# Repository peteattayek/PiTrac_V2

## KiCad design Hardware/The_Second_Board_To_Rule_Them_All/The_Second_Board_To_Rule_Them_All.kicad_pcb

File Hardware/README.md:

# PiTrac V2 — Hardware

KiCad design and RP2354 firmware for the PiTrac launch monitor controller board:
*"The Second Board To Rule Them All"*, Rev V1.

> **New to this repo?** Start with [`../DEVELOPER_GUIDE.md`](../DEVELOPER_GUIDE.md). It covers
> the repo map, the full pinout, how the firmware is built and why, and what is not done yet.

The board detects a golf ball crossing an IR light curtain, measures its speed from
the beam transit time, triggers two Mira220 global-shutter cameras, and fires a
high-power IR strobe in a precisely timed burst so each camera freezes the ball
~10 times in a single exposure. A Raspberry Pi 5 rides on top — powered *by* this
board through the 40-pin header — and handles image pull and analysis.

**The RP2354 owns everything with microsecond timing requirements. The Pi owns
everything with pixels.**

---

## Layout

```
Hardware/
├── The_Second_Board_To_Rule_Them_All.md     ← design document: theory of operation,
│                                              subsystem detail, test points, pin map
├── The_Second_Board_To_Rule_Them_All/       ← KiCad 10 project, 8 sheets
│   ├── *.kicad_sch, *.kicad_pcb
│   ├── *.net                                 netlist export (firmware is verified against this)
│   └── jlcpcb/production_files/              gerbers + BOM + CPL as sent to fab
└── firmware/                                ← RP2354B firmware, C / Pico SDK 2.x
```

`../HARDWARE_REFERENCE.md` (repo root) is **generated** from the netlist by
`firmware/tools/netlist_report.py`. Regenerate it rather than editing it.

### Camera calibration

[Calibration/README.md](Calibration/README.md) contains the camera-distortion
procedure, A4/Letter ChArUco print templates, capture checklist, and session/result
records. Use a separate calibration for each identified physical camera/lens
stack at its final filter, illumination, and locked-focus state. Digital target
checks do not establish physical print quality or calibrated camera coefficients.

### Firmware documents, in reading order

| File | What it is |
|---|---|
| **`firmware/START_HERE.md`** | **Start here if you have never built Pico firmware.** Toolchain install, build, flash, first CLI commands. Assumes no C or embedded experience. |
| `firmware/HANDOFF.md` | Working conventions, safety rules, tooling traps and hard-won measurement lessons, for anyone taking over the bench work. |
| `firmware/PROGRESS.md` | **The living record.** What is done, open questions with where each gets resolved, recent bench measurements, the decisions behind the design, and the code-audit backlog. §0 and §10 hold the live status. Read before changing anything. |
| `firmware/PROGRESS_ARCHIVE.md` | Closed history moved verbatim out of PROGRESS.md (older measurement log, superseded resume blocks, dated Phase 3 results). Nothing in it is current status. |
| `firmware/ARCHITECTURE.md` | Hardware-offload audit — what runs on PIO/PWM/DMA versus the CPU, and why. |
| `firmware/BRINGUP_NEW_BOARD.md` | **The driver for a newly assembled board.** Only the per-board steps, in order, with a sign-off table. |
| `firmware/BENCH.md` | Bring-up procedures, phases 0 → 1c. |
| `firmware/BENCH_P2_BEAM.md` | Phase 2 — beam carrier and phase-locked demodulator. |
| `firmware/BENCH_P3_DETECT.md` | Phases 3 & 4 — photodiode chain and trigger selection. |
| `firmware/BENCH_P5_P7_MIC_CAMERA.md` | Phases 5 & 7 — microphone and cameras. |
| `firmware/BENCH_P6_STROBE.md` | Phase 6 — ⚠ 9 A pulses, linear-mode FET. Read fully before powering. |
| `firmware/BENCH_P8_PI.md` | Phase 8 — real Pi 5 integration and clean-shutdown acceptance. |
| `firmware/NEXT_BOARD_REV.md` | Hardware change requests (CR-xx) for the next board spin. |
| `firmware/SETUP.md` | Toolchain detail and the manual (non-VS-Code) install path. |

---

## Status

Bring-up is staged, and each phase is independently provable on the bench before
the next begins. **The live status is always `firmware/PROGRESS.md` §0 and the top
block of §10** — this table is a summary as of 2026-10-05.

| Phase | |
|---|---|
| 0 · toolchain, CLI, ADC/DMA capture | ✅ |
| 0.5 · rails, boost, virtual ground | ✅ |
| 1 · power button, latch, supply guards | ✅ (Test 6, stale power requests: ✅ owner-reported 2026-09-28) |
| 1b · Pi soft-shutdown vs. a simulated Pi | ✅ |
| 1c · panel indicators | ✅ |
| 2 · beam carrier + demod phase lock | ✅ |
| 3 · photodiode chain and calibration | 🟡 §3.1–3.6 done on board 3; first real ball waveform passed; comparator timing and the 20-pass set are open |
| 4 · trigger-source experiment | 🟡 firmware written, bench not started |
| 5 · microphone | 🟡 front end validated; no onset-detection or veto firmware yet |
| 6 · strobe | 🟡 **6a/6b dry tests PASS on board 1 (2026-10-06)** — U5 clamp 135 µs, PIO timing, schedule, A7, interlock, gate DAC. **6c/6d live-current firmware written 2026-10-07** (guarded: staircase, 70 % ceiling, ADC0 readback per firing, overcurrent/stuck-on faults, watchdog); TP3 loop stability PASS 2026-10-08; 6c on board 1 up to 24 % after a gate-drive rework (CR-23); **6d PASS 2026-10-15**; next is the ADC0 readback fix |
| 7 · cameras | ❌ no firmware yet; blocked on the 1.8 V I/O translator (CR-09) |
| 8 · Pi integration | 🟡 power and shutdown handshake done; UART protocol not written |

---

## Safety rules that outrank convenience

1. **No Pi 5 on J8 until Phase 7c.** The +5 V latch *is* the Pi's power switch, and any
   RP2354 reset — SW2, `reset`, `bootsel`, the watchdog, a brownout — opens it: a hard power
   cut, not a reboot.
2. **`PULSE_LIMIT_DISABLE` (GPIO27) stays 0.** It defeats the strobe hardware
   watchdog. It is written in exactly one place in the firmware and there is
   deliberately no CLI path to it.
3. **Never run the +5 V rail from USB power.** Two independent guards enforce this;
   both exist because the failure mode is a Pi 5 fed through a 1 A diode.
4. **Do not connect J4 (cameras).** The Mira220 I/O is 1.8 V with no 3.3 V tolerance
   (answered 2026-08-14). J4 needs a level translator first — `firmware/NEXT_BOARD_REV.md`
   CR-09.
5. **Nothing conductive near the photodiode D12.** Its cathode sits at 36 V; foil across it
   destroyed an op-amp on board 1.

---

## Building the firmware

```
cd firmware
cmake -B build -G Ninja -DCMAKE_BUILD_TYPE=Release
cmake --build build
```

Needs Pico SDK **2.1+** (the project pins 2.3.0) and an ARM toolchain — `firmware/SETUP.md`
covers both, and the VS Code Pico extension installs everything itself if you would rather
not. The extension keeps its tools in `~/.pico-sdk` and does **not** put them on `PATH`;
see `firmware/HANDOFF.md` §4 for the command-line build.

The board is an **RP2354B**: RP2350B core, 48 GPIO, 2 MB stacked internal flash,
**ARM** (not RISC-V). `CMakeLists.txt` forces the correct board and there is a
compile-time assert that fails loudly if anything overrides it.

---

## Design corrections

The design document predates bring-up, and several of its numbers were superseded by
measurement. The evidence is in `firmware/PROGRESS.md`; the full list is in
[`../DEVELOPER_GUIDE.md`](../DEVELOPER_GUIDE.md) §4. The ones most worth knowing:

- **The virtual ground is not 2.50 V.** R75/R76 = 10K/10K makes it literally
  +5VA ÷ 2 — measured **2.59 V** on the 5.2 V rail. It also moves with the rail (CR-02).
- **The one-shot clamp is 122.68 µs** (U9, measured in Phase 2c), not the .md's 113 µs
  and not the 86 µs the datasheet's K ≈ 0.7 predicted. U5, the strobe one-shot, is still
  unmeasured.
- **`cal_demod_phase()` in §13.8 cannot work as written** — it samples after a
  0.66 s high-pass with a *static* reflector, so it reads noise at every phase. The
  firmware's chopped-beam `cal demod` replaces it.
- **RPI5_SHUTDOWN is active-low**, matching the default `gpio-shutdown` overlay —
  confirmed on hardware as a 200 ms low pulse. The .md pseudocode is backwards.
- **The PWM slice numbers in the .md are RP2040 numbering.** On the RP2350B the beam
  carrier is slice 7B, the demod clock 11B and the gate DAC 6A — which collides with the
  ready LED (CR-01).
- **`HPF_Toggle` low is TRACK**, not HOLD.

---

## License

See [`../LICENSING.md`](../LICENSING.md). Board design files are **CERN-OHL-S v2**
(`../LICENSES/CERN-OHL-S-2.0.txt`); firmware and host tools are **GPL-3.0-or-later**
(`../LICENSE`).

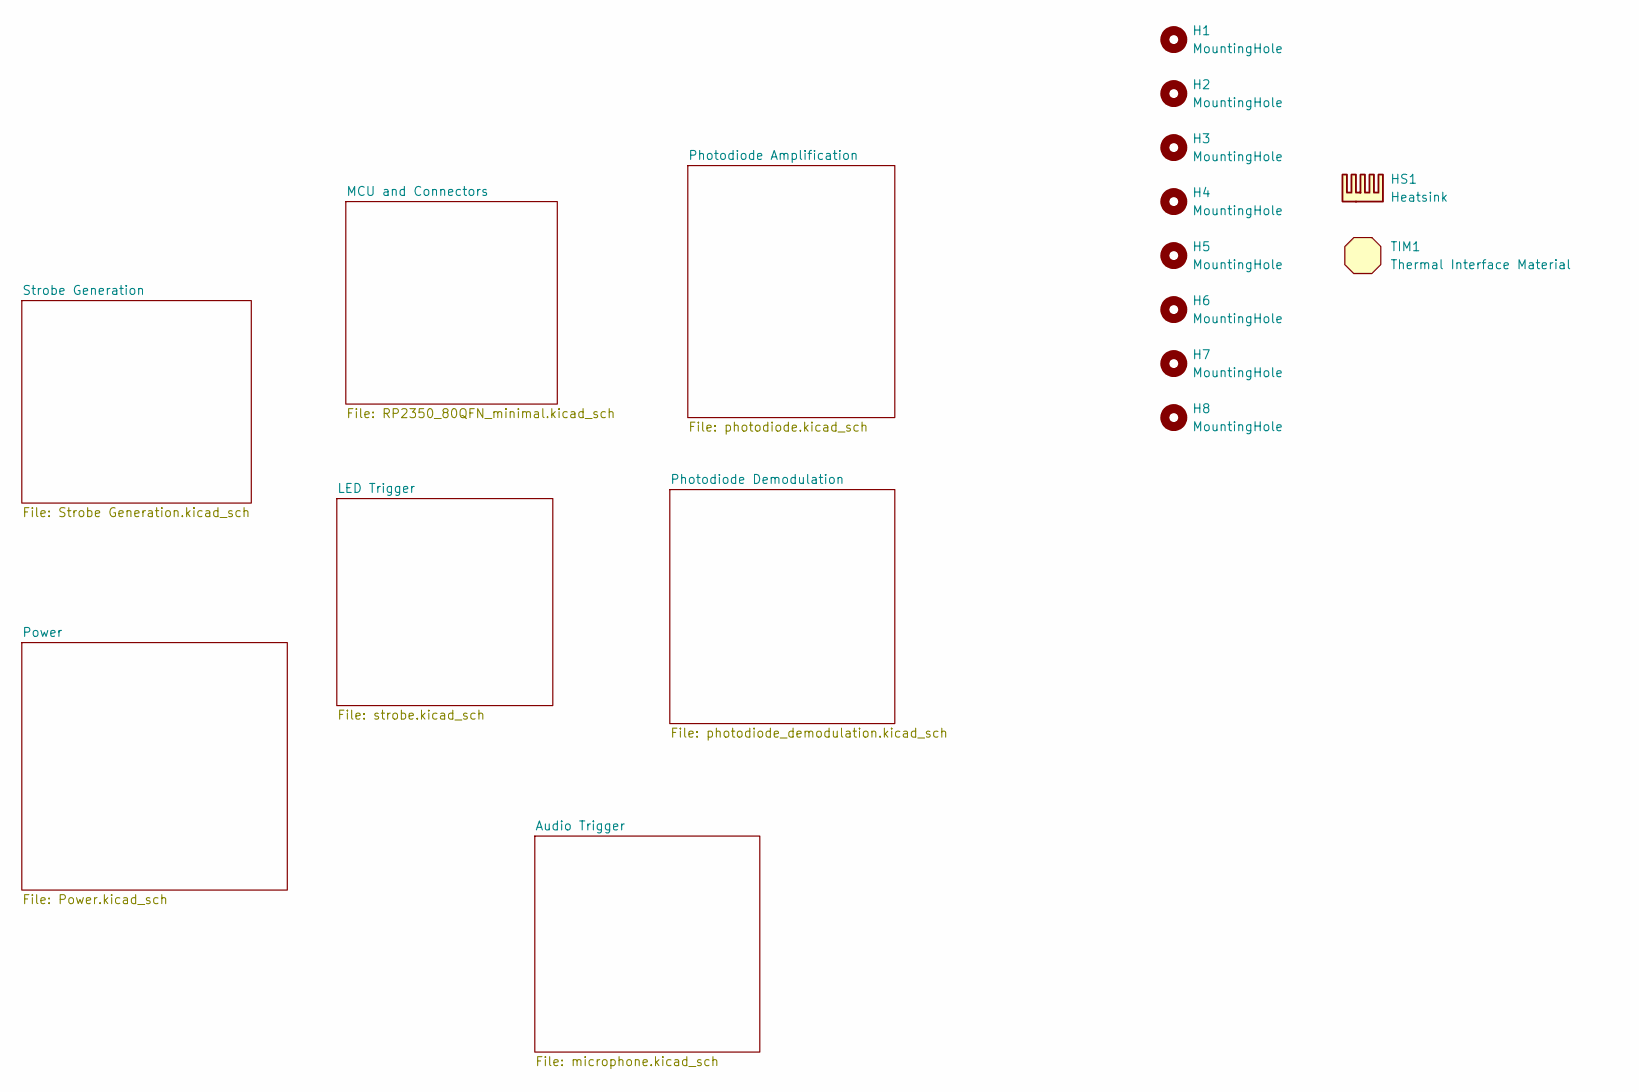
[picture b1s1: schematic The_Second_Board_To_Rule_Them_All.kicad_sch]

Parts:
H1, H2, H7, H8: MountingHole; MountingHole_2.2mm_M2
H3, H4, H5, H6: MountingHole; MountingHole_2.7mm_M2.5
HS1: Heatsink; Ratings <= 27 C/W; MPN HSB09-212115
TIM1: Thermal Interface Material; MPN TG-T1000-20-20-0.25-5PT

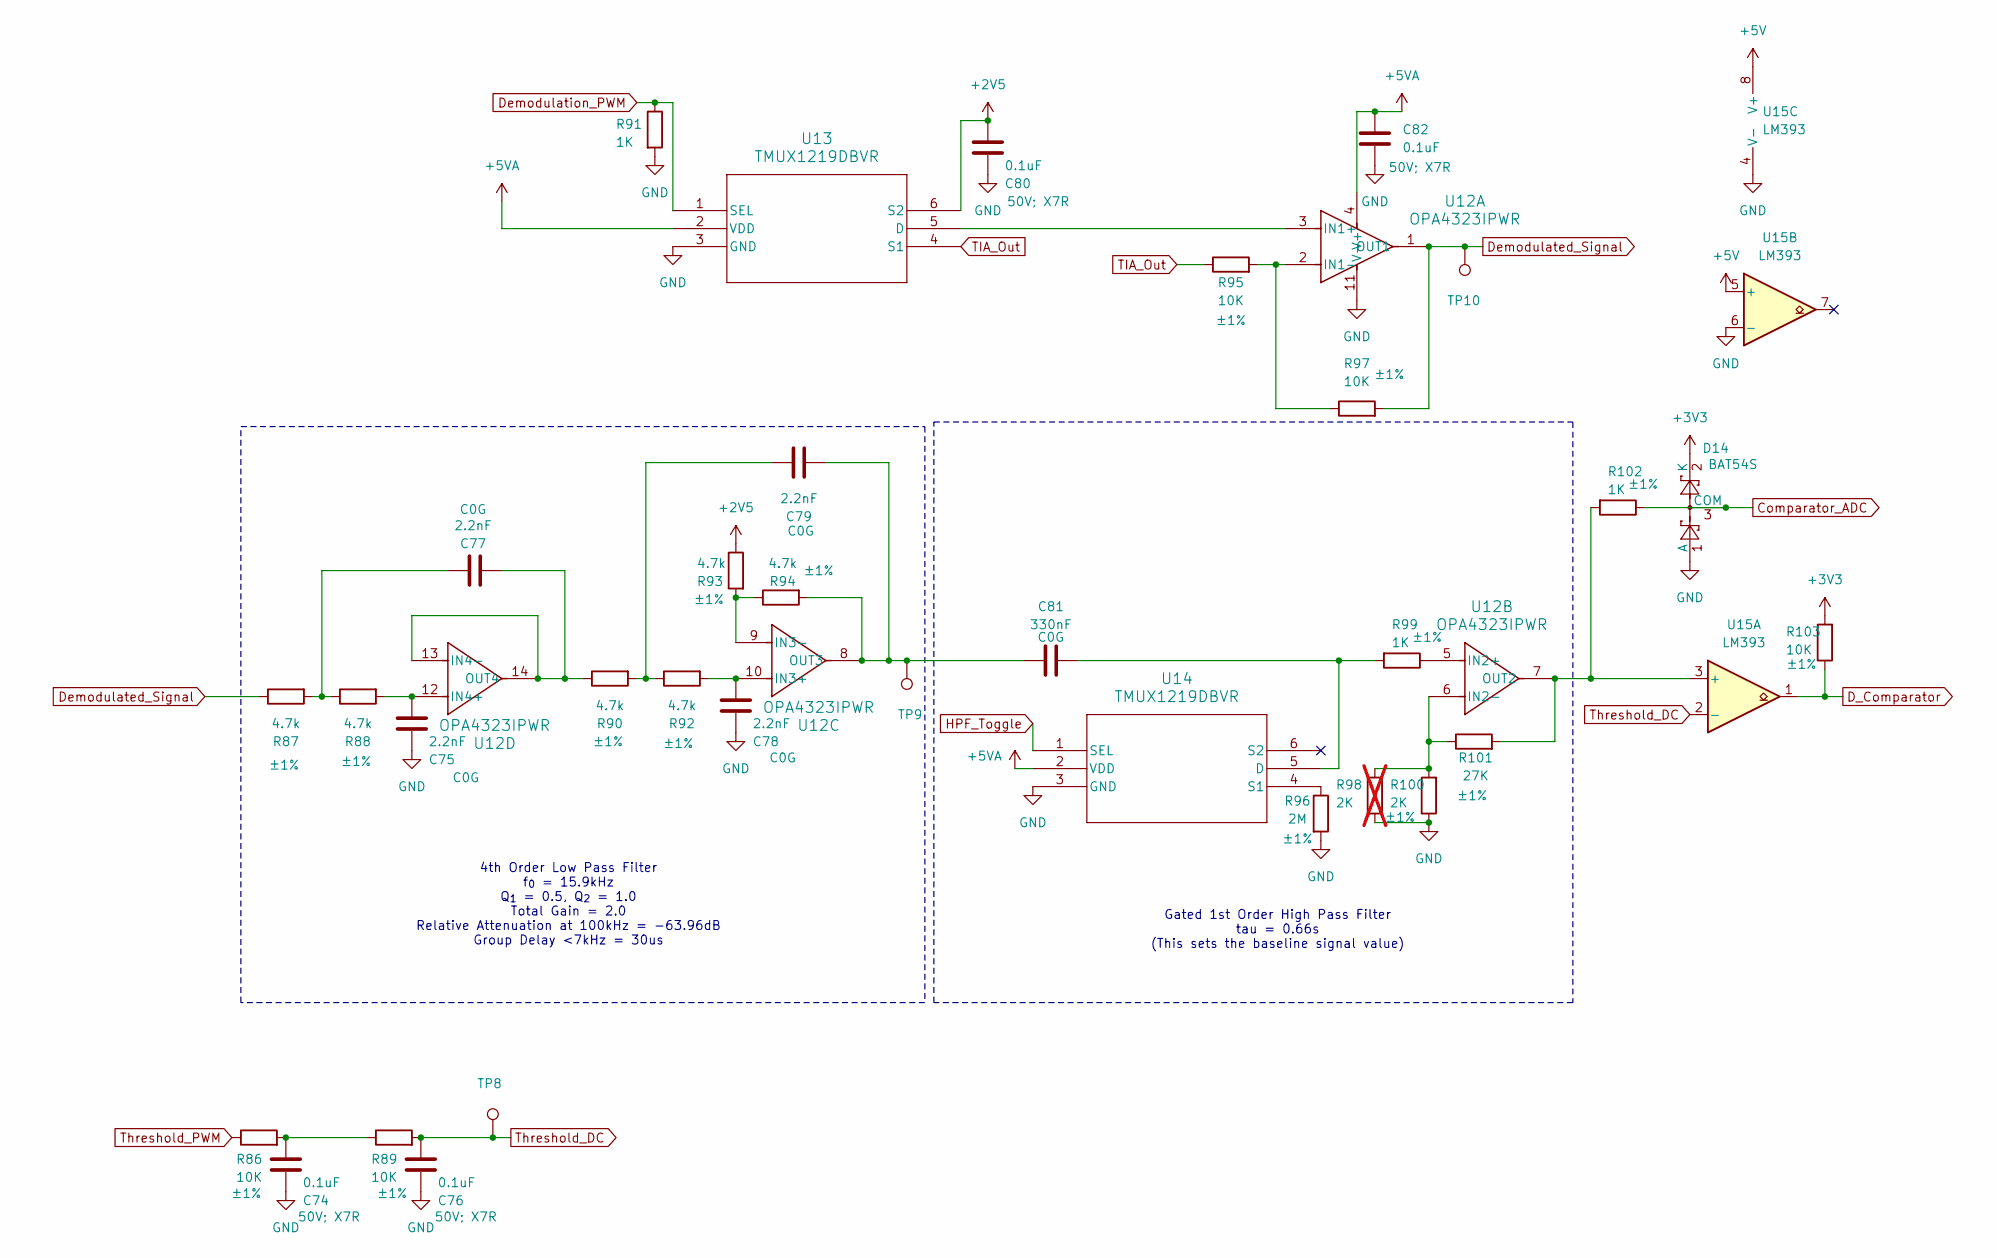
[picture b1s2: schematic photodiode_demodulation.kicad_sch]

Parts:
C74, C76, C80, C82: 0.1uF; C_0402_1005Metric; Ratings 50V; X7R; MPN CL05B104KB54PNC; LCSC C307331
C75, C77, C78, C79: 2.2nF; C_0805_2012Metric; Ratings C0G; MPN CL21C222JBFNNNE; LCSC C28260
C81: 330nF; C_1206_3216Metric; Ratings C0G; MPN GRM31C5C1E334JE01L; LCSC C3837965
D14: BAT54S; SOT-23; MPN BAT54SLT1G; LCSC C7420333
R86, R89, R95, R97, R103: 10K; R_0402_1005Metric; Ratings ±1%; MPN RMCF0402FT10K0; LCSC C25744
R87, R88, R90, R92, R93, R94: 4.7k; R_0402_1005Metric; Ratings ±1%; MPN RMCF0402FT4K70; LCSC C25900
R91, R99, R102: 1K; R_0402_1005Metric; Ratings ±1%; MPN RMCF0402FT1K00; LCSC C11702
R96: 2M; R_0603_1608Metric; Ratings ±1%; MPN RMCF0603FT2M00; LCSC C22976
R98: 2K; R_0805_2012Metric_Pad1.20x1.40mm_HandSolder; Ratings ±1%; MPN RMCF0805FT2K00; not fitted
R100: 2K; R_0805_2012Metric_Pad1.20x1.40mm_HandSolder; Ratings ±1%; MPN RMCF0805FT2K00; LCSC C17604
R101: 27K; R_0402_1005Metric; Ratings ±1%; MPN RMCF0402FT27K0; LCSC C25771
TP8, TP9, TP10: TestPoint; TestPoint_THTPad_D1.0mm_Drill0.5mm
U12: OPA4323IPWR; PW0014A-IPC_A; MPN OPA4323IPWR; LCSC C22419728
U13, U14: TMUX1219DBVR; SOT-23-6_DBV_TEX; MPN TMUX1219DBVR; LCSC C2869838
U15: LM393; SOIC-8_3.9x4.9mm_P1.27mm; MPN LM393DR2G; Digikey PN LM393DR2GOSCT-ND

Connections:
+2V5: C80.2, R93.1, U13.6 (S2); also elsewhere on the board
+3V3: D14.2 (K), R103.2; also elsewhere on the board
+5V: U15.5 (+), U15.8 (V+); also elsewhere on the board
+5VA: C82.1, U12.4 (V+), U13.2 (VDD), U14.2 (VDD); also elsewhere on the board
Comparator_ADC: D14.3 (COM), R102.1; also elsewhere on the board
D_Comparator: R103.1, U15.1; also elsewhere on the board
Demodulated_Signal: R87.1, R97.2, TP10.1 (1_1), U12.1 (OUT1)
Demodulation_PWM: R91.1, U13.1 (SEL); also elsewhere on the board
GND: C74.1, C75.1, C76.1, C78.1, C80.1, C82.2, D14.1 (A), R91.2, R96.2, R98.1, R100.1, U12.11 (V-), U13.3 (GND), U14.3 (GND), U15.4 (V-), U15.6 (-); also elsewhere on the board
HPF_Toggle: U14.1 (SEL); also elsewhere on the board
unnamed: C74.2, R86.2, R89.1
unnamed: C77.1, R87.2, R88.1
unnamed: C79.1, R90.2, R92.1
unnamed: U12.3 (IN1+), U13.5 (D)
unnamed: R95.2, R97.1, U12.2 (IN1-)
unnamed: R99.1, U12.5 (IN2+)
unnamed: R98.2, R100.2, R101.1, U12.6 (IN2-)
unnamed: R101.2, R102.2, U12.7 (OUT2), U15.3 (+)
unnamed: C78.2, R92.2, U12.10 (IN3+)
unnamed: R93.2, R94.1, U12.9 (IN3-)
unnamed: C79.2, C81.1, R94.2, TP9.1 (1_1), U12.8 (OUT3)
unnamed: C75.2, R88.2, U12.12 (IN4+)
unnamed: C77.2, R90.1, U12.13 (IN4-), U12.14 (OUT4)
unnamed: C81.2, R99.2, U14.5 (D)
unnamed: R96.1, U14.4 (S1)
TIA_Out: R95.1, U13.4 (S1); also elsewhere on the board
Threshold_DC: C76.2, R89.2, TP8.1 (1_1), U15.2 (-)
Threshold_PWM: R86.1; also elsewhere on the board

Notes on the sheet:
Gated 1st Order High Pass Filter tau = 0.66s (This sets the baseline signal value)
4th Order Low Pass Filter f_{0} = 15.9kHz Q_{1} = 0.5, Q_{2} = 1.0 Total Gain = 2.0 Relative Attenuation at 100kHz = -63.96dB Group Delay <7kHz = 30us

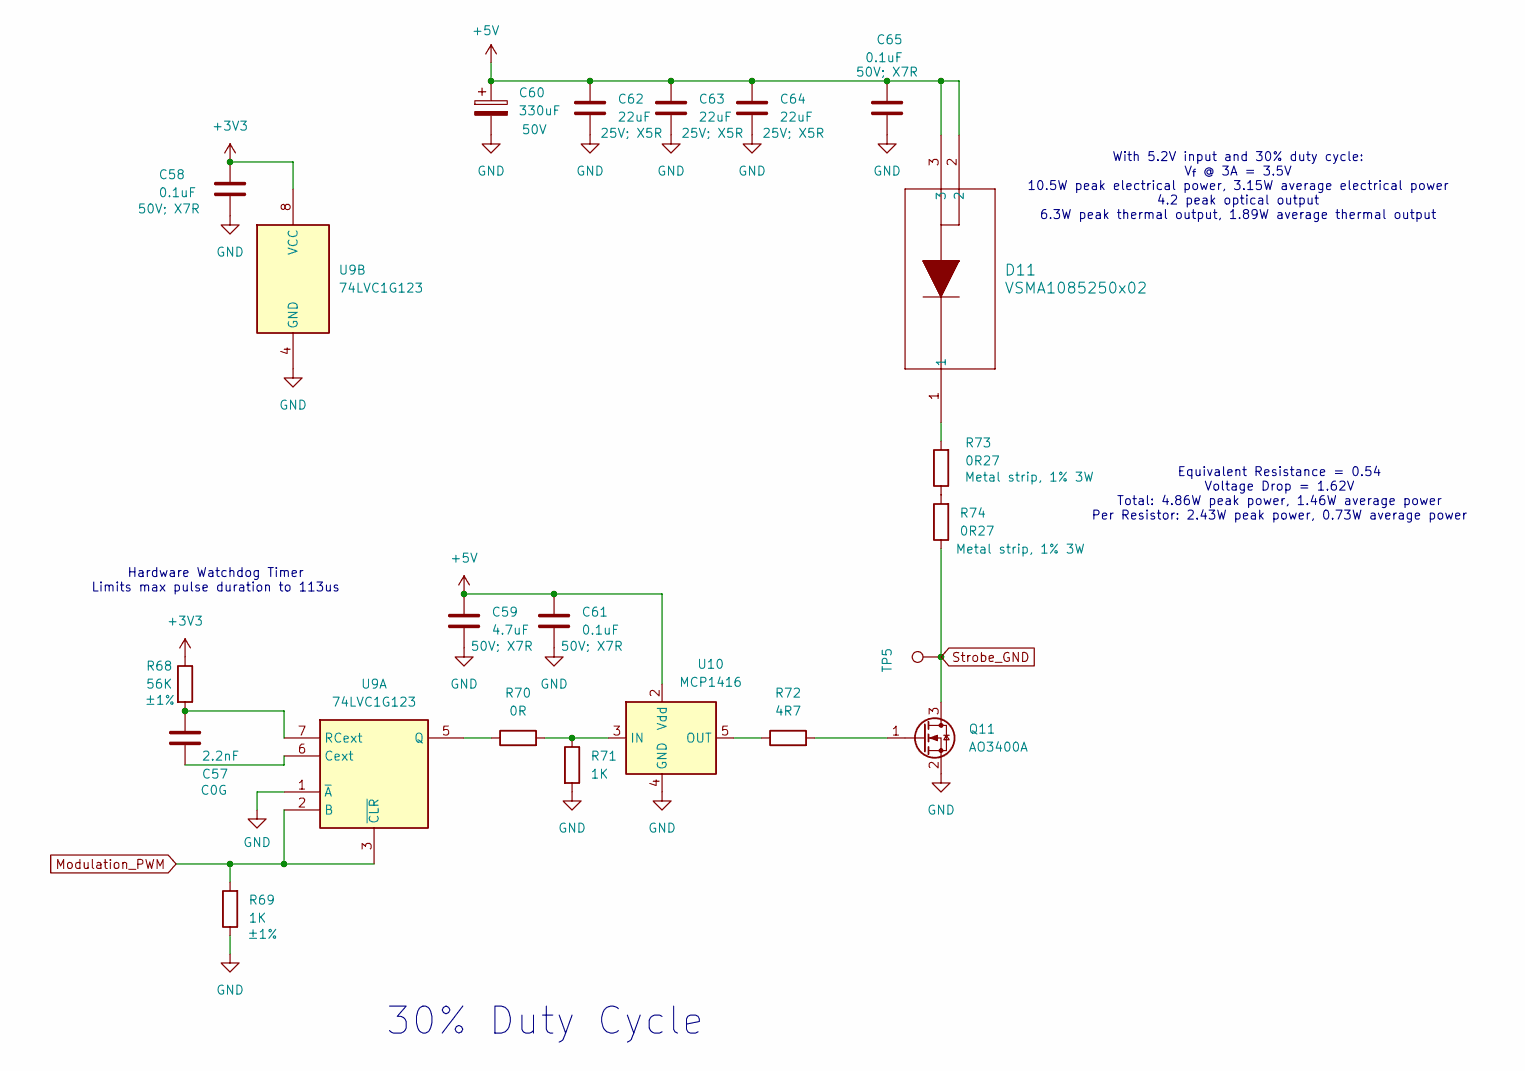
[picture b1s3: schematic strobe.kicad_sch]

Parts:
C57: 2.2nF; C_0805_2012Metric; Ratings C0G; MPN CL21C222JBFNNNE; LCSC C28260
C58, C61, C65: 0.1uF; C_0402_1005Metric; Ratings 50V; X7R; MPN CL05B104KB54PNC; LCSC C307331
C59: 4.7uF; C_1206_3216Metric; Ratings 50V; X7R; MPN CL31B475KBHNFNE; LCSC C29823
C60: 330uF; CAP_50TPV_10x10.5_RBY; Ratings 50V; MPN 50TPV330M10X10.5; LCSC C53120968
C62, C63, C64: 22uF; C_1206_3216Metric; Ratings 25V; X5R; MPN CL31A226KAHNNNE; LCSC C12891
D11: VSMA1085250x02; DIODE_VSMA1085250_VIS; MPN VSMA1085250X02; LCSC C20346087
Q11: AO3400A; SOT-23; MPN AO3400A; Digikey PN 785-1000-1-ND
R68: 56K; R_0603_1608Metric; Ratings ±1%; MPN RMCF0603FT56K0; LCSC C23206
R69, R71: 1K; R_0402_1005Metric; Ratings ±1%; MPN RMCF0402FT1K00; LCSC C11702
R70: 0R; R_0805_2012Metric_Pad1.20x1.40mm_HandSolder; MPN RMCF0805ZT0R00; LCSC C17477
R72: 4R7; R_0805_2012Metric; Ratings ±1%; MPN RMCF0805FT4R70; LCSC C17675
R73, R74: 0R27; R_2512_6332Metric; Ratings Metal strip, 1% 3W; MPN HoJLR2512-3W-270mR-1%; LCSC C2903472
TP5: TestPoint; TestPoint_THTPad_D1.0mm_Drill0.5mm
U9: 74LVC1G123; VSSOP-8_2.3x2mm_P0.5mm; MPN SN74LVC1G123DCUR; LCSC C26159250
U10: MCP1416; SOT-23-5; MPN MCP1416T-E/OT; LCSC C83775

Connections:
+3V3: C58.1, R68.1, U9.8 (VCC); also elsewhere on the board
+5V: C59.1, C60.1, C61.1, C62.1, C63.1, C64.1, C65.2, D11.2, D11.3, U10.2 (Vdd); also elsewhere on the board
GND: C58.2, C59.2, C60.2, C61.2, C62.2, C63.2, C64.2, C65.1, Q11.2 (S), R69.1, R71.2, U9.1 (~A), U9.4 (GND), U10.4 (GND); also elsewhere on the board
Modulation_PWM: R69.2, U9.2 (B), U9.3 (~CLR); also elsewhere on the board
unnamed: D11.1, R73.2
unnamed: Q11.1 (G), R72.2
unnamed: R73.1, R74.2
unnamed: C57.1, U9.6 (Cext)
unnamed: R70.1, U9.5 (Q)
unnamed: C57.2, R68.2, U9.7 (RCext)
unnamed: R70.2, R71.1, U10.3 (IN)
unnamed: R72.1, U10.5 (OUT)
Strobe_GND: Q11.3 (D), R74.1, TP5.1 (1_1)

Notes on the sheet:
Hardware Watchdog Timer Limits max pulse duration to 113us
30% Duty Cycle
With 5.2V input and 30% duty cycle: V_{f} @ 3A = 3.5V 10.5W peak electrical power, 3.15W average electrical power 4.2 peak optical output 6.3W peak thermal output, 1.89W average thermal output
Equivalent Resistance = 0.54 Voltage Drop = 1.62V Total: 4.86W peak power, 1.46W average power Per Resistor: 2.43W peak power, 0.73W average power

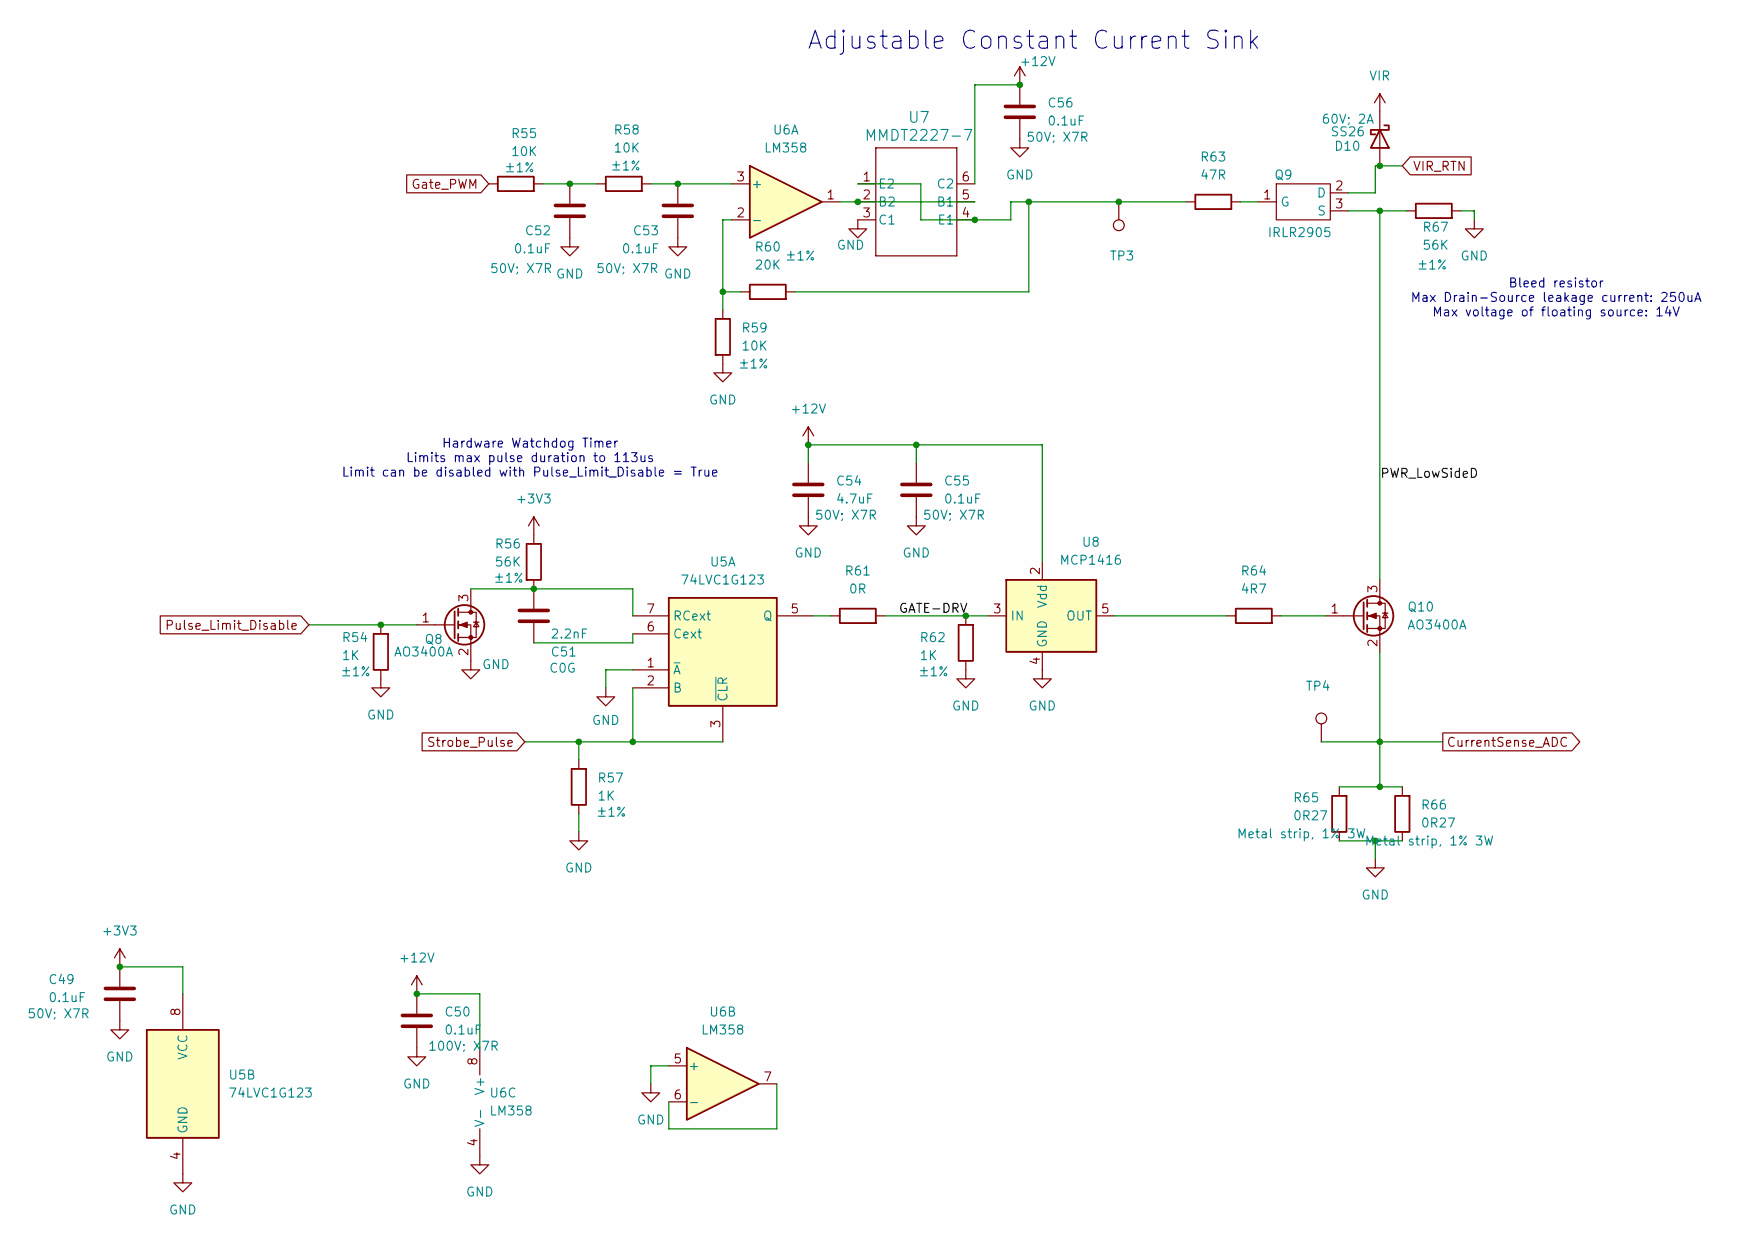
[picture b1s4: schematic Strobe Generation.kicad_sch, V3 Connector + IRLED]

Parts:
C49, C52, C53, C55, C56: 0.1uF; C_0402_1005Metric; Ratings 50V; X7R; MPN CL05B104KB54PNC; LCSC C307331
C50: 0.1uF; C_0805_2012Metric; Ratings 100V; X7R; MPN CL21B104KCFNNNE; LCSC C28233
C51: 2.2nF; C_0805_2012Metric; Ratings C0G; MPN CL21C222JBFNNNE; LCSC C28260
C54: 4.7uF; C_1206_3216Metric; Ratings 50V; X7R; MPN CL31B475KBHNFNE; LCSC C29823
D10: SS26; D_SMA; Ratings 60V; 2A; MPN SS26S-E3/5AT; LCSC C7420363
Q8, Q10: AO3400A; SOT-23; MPN AO3400A; Digikey PN 785-1000-1-ND
Q9: IRLR2905; ThermalVias; MPN IRLR2905TRPBF; LCSC C3010
R54, R57, R62: 1K; R_0402_1005Metric; Ratings ±1%; MPN RMCF0402FT1K00; LCSC C11702
R55, R58, R59: 10K; R_0402_1005Metric; Ratings ±1%; MPN RMCF0402FT10K0; LCSC C25744
R56, R67: 56K; R_0603_1608Metric; Ratings ±1%; MPN RMCF0603FT56K0; LCSC C23206
R60: 20K; R_0402_1005Metric; Ratings ±1%; MPN RMCF0402FT20K0; LCSC C25765
R61: 0R; R_0805_2012Metric_Pad1.20x1.40mm_HandSolder; MPN RMCF0805ZT0R00; LCSC C17477
R63: 47R; R_0402_1005Metric; Ratings ±1%; MPN RMCF0402FT47R0; LCSC C25118
R64: 4R7; R_0805_2012Metric; Ratings ±1%; MPN RMCF0805FT4R70; LCSC C17675
R65, R66: 0R27; R_2512_6332Metric; Ratings Metal strip, 1% 3W; MPN HoJLR2512-3W-270mR-1%; LCSC C2903472
TP3, TP4: TestPoint; TestPoint_THTPad_D1.0mm_Drill0.5mm
U5: 74LVC1G123; VSSOP-8_2.3x2mm_P0.5mm; MPN SN74LVC1G123DCUR; LCSC C26159250
U6: LM358; SOIC-8_3.9x4.9mm_P1.27mm; MPN LM358DR2G; LCSC C7950
U7: MMDT2227-7; SOT-363_DIO; MPN MMDT2227-7-F; LCSC C41375117
U8: MCP1416; SOT-23-5; MPN MCP1416T-E/OT; LCSC C83775

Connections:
+3V3: C49.1, R56.1, U5.8 (VCC); also elsewhere on the board
+12V: C50.1, C54.1, C55.1, C56.1, U6.8 (V+), U7.6 (C2), U8.2 (Vdd); also elsewhere on the board
/Strobe Generation/GATE-DRV: R61.2, R62.2, U8.3 (IN)
/Strobe Generation/PWR_LowSideD: Q9.3 (S), Q10.3 (D), R67.1
CurrentSense_ADC: Q10.2 (S), R65.2, R66.2, TP4.1 (1_1); also elsewhere on the board
GND: C49.2, C50.2, C52.1, C53.1, C54.2, C55.2, C56.2, Q8.2 (S), R54.1, R57.1, R59.2, R62.1, R65.1, R66.1, R67.2, U5.1 (~A), U5.4 (GND), U6.4 (V-), U6.5 (+), U7.3 (C1), U8.4 (GND); also elsewhere on the board
Gate_PWM: R55.1; also elsewhere on the board
unnamed: C52.2, R55.2, R58.1
unnamed: C51.2, Q8.3 (D), R56.2, U5.7 (RCext)
unnamed: Q9.1 (G), R63.2
unnamed: Q10.1 (G), R64.2
unnamed: C51.1, U5.6 (Cext)
unnamed: R61.1, U5.5 (Q)
unnamed: C53.2, R58.2, U6.3 (+)
unnamed: R59.1, R60.1, U6.2 (-)
unnamed: U6.6 (-), U6.7
unnamed: U6.1, U7.2 (B2), U7.5 (B1)
unnamed: R60.2, R63.1, TP3.1 (1_1), U7.1 (E2), U7.4 (E1)
unnamed: R64.1, U8.5 (OUT)
Pulse_Limit_Disable: Q8.1 (G), R54.2; also elsewhere on the board
Strobe_Pulse: R57.2, U5.2 (B), U5.3 (~CLR); also elsewhere on the board
VIR: D10.1 (K); also elsewhere on the board
VIR_RTN: D10.2 (A), Q9.2 (D); also elsewhere on the board

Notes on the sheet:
Hardware Watchdog Timer Limits max pulse duration to 113us Limit can be disabled with Pulse_Limit_Disable = True
Adjustable Constant Current Sink
Bleed resistor Max Drain-Source leakage current: 250uA Max voltage of floating source: 14V

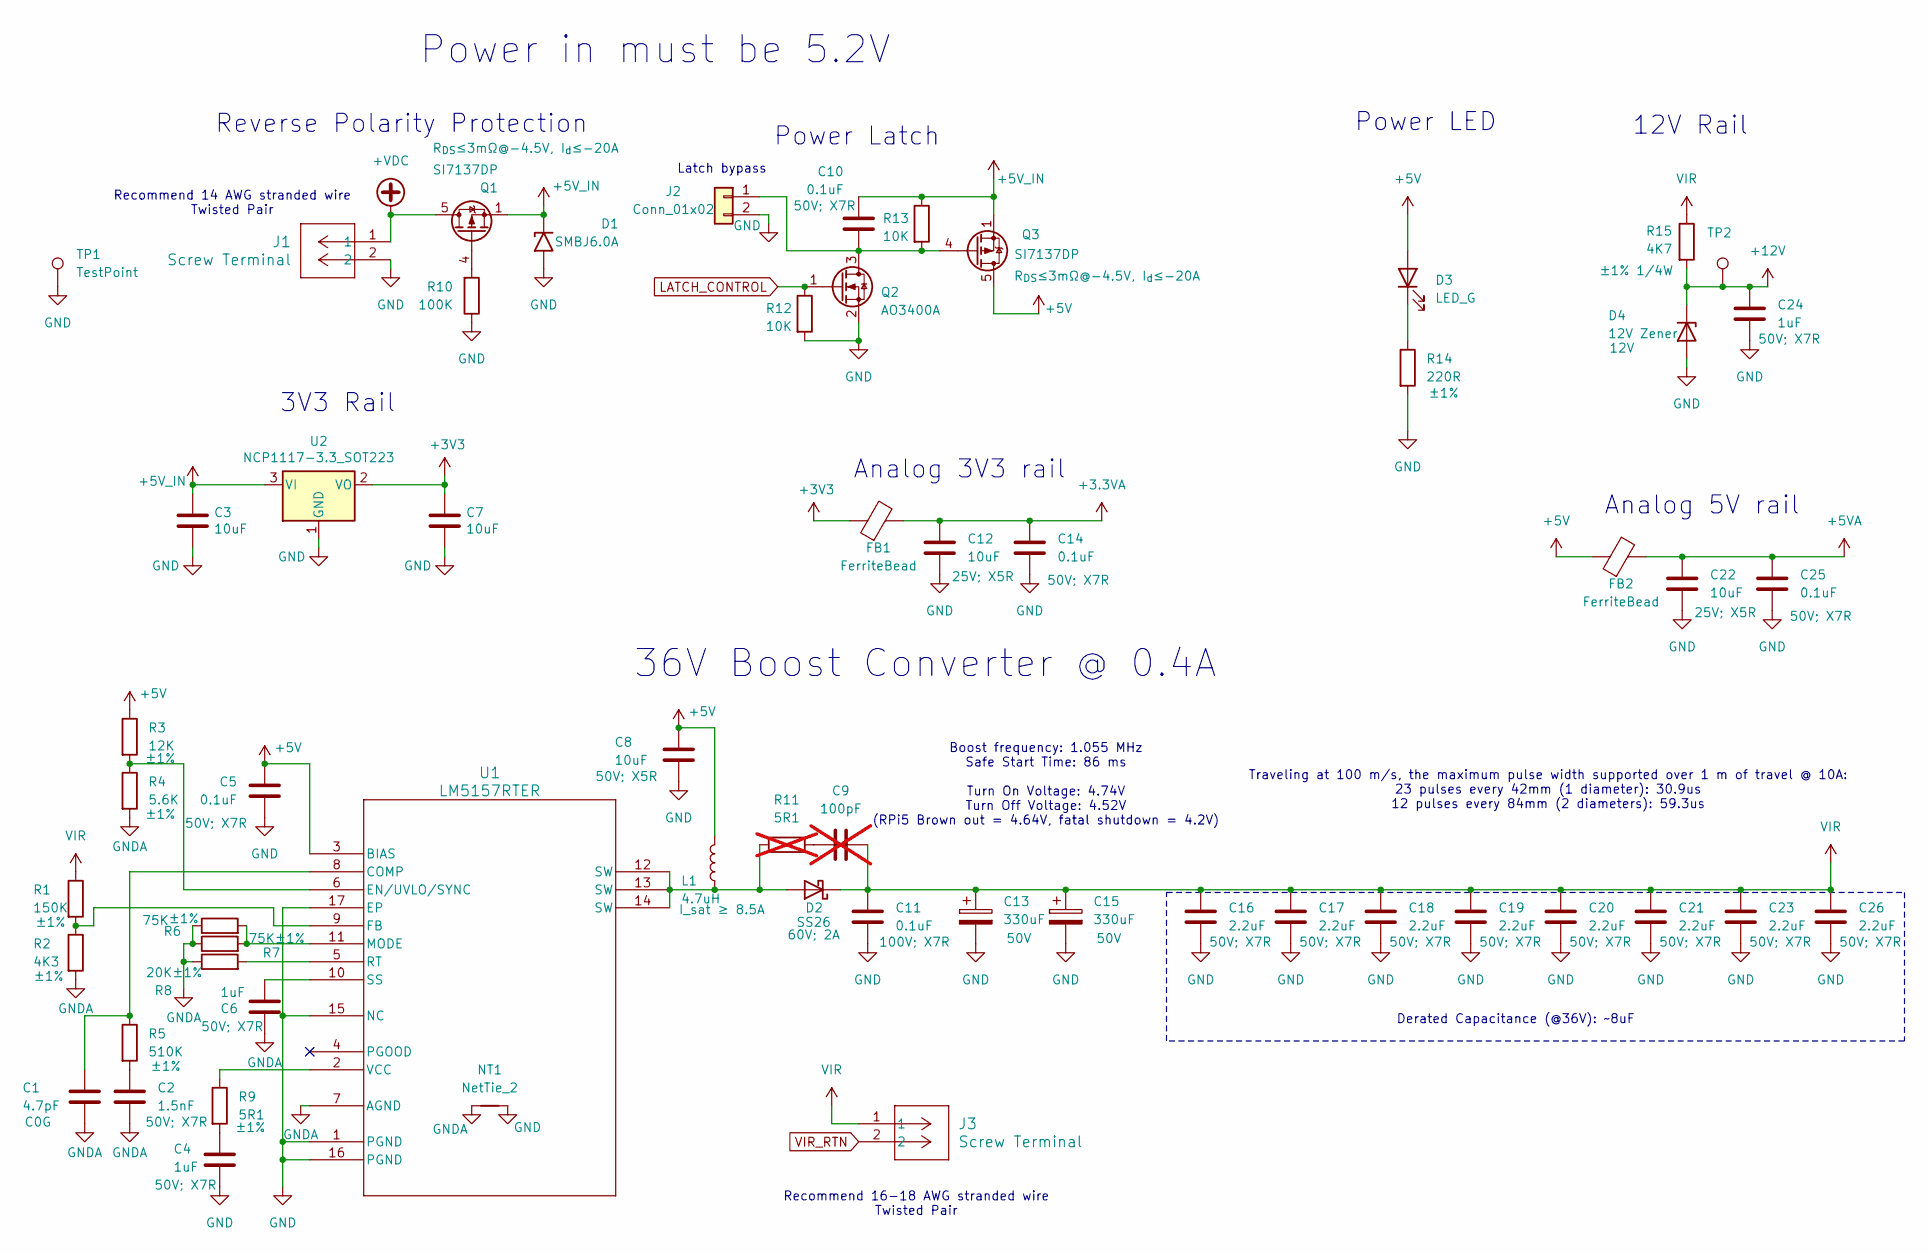
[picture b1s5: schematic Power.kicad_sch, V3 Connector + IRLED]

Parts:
C1: 4.7pF; C_0402_1005Metric; Ratings C0G; MPN GRM1555C1H4R7CA01D; LCSC C1569
C2: 1.5nF; C_0603_1608Metric; Ratings 50V; X7R; MPN GCD188R71H152KA01D; LCSC C1595
C3, C7, C12, C22: 10uF; C_0603_1608Metric; Ratings 25V; X5R; MPN CL10A106MA8NRNC; LCSC C96446
C4, C6, C24: 1uF; C_0805_2012Metric; Ratings 50V; X7R; MPN CL21B105KBFNNNE; LCSC C28323
C5, C10, C14, C25: 0.1uF; C_0402_1005Metric; Ratings 50V; X7R; MPN CL05B104KB54PNC; LCSC C307331
C8: 10uF; C_0805_2012Metric; Ratings 50V; X5R; MPN GRM21BR61H106KE43L; LCSC C440198
C9: 100pF; C_0603_1608Metric; Ratings 100V, C0G; MPN GCM1885C2A101JA16D; not fitted
C11: 0.1uF; C_0805_2012Metric; Ratings 100V; X7R; MPN CL21B104KCFNNNE; LCSC C28233
C13, C15: 330uF; CAP_50TPV_10x10.5_RBY; Ratings 50V; MPN 50TPV330M10X10.5; LCSC C53120968
C16, C17, C18, C19, C20, C21, C23, C26: 2.2uF; C_1206_3216Metric; Ratings 50V; X7R; MPN CL31B225KBHNNNE; LCSC C50254
D1: SMBJ6.0A; D_SMB; MPN SMBJ6.0A; LCSC C19077560
D2: SS26; D_SMA; Ratings 60V; 2A; MPN SS26S-E3/5AT; LCSC C7420363
D3: LED_G; LED_0805_2012Metric; MPN APT2012LZGCK; LCSC C2297
D4: 12V Zener; D_SOD-123; Ratings 12V; MPN BZT52B12; LCSC C22395569
FB1, FB2: FerriteBead; L_0603_1608Metric; MPN BLM18PG121SN1D; LCSC C14709
J1, J3: Screw Terminal; CONN2_710002_WRE; MPN 691137710002
J2: Conn_01x02; PinHeader_1x02_P2.54mm_Vertical; MPN PH1-02-UA
L1: 4.7uH; L_Abracon_ASPI-0630LR; Ratings I_sat ≥ 8.5A; MPN ASPI-0630HI-4R7M-T15; LCSC C207840
NT1: NetTie_2; NetTie-2_SMD_Pad0.5mm
Q1, Q3: SI7137DP; PQFN-8-EP_6x5mm_P1.27mm_Generic_ThermalVias; Ratings R_{DS}≤3mΩ@-4.5V, I_{d}≤-20A; MPN SI7137DP-T1-GE3; LCSC C42456927
Q2: AO3400A; SOT-23; MPN AO3400A; LCSC C20917
R1: 150K; R_0603_1608Metric; Ratings ±1%; MPN RMCF0603FT150K; LCSC C22807
R2: 4K3; R_0603_1608Metric; Ratings ±1%; MPN RMCF0603FT4K30; LCSC C23159
R3: 12K; R_0603_1608Metric; Ratings ±1%; MPN RMCF0603FT12K0; LCSC C22790
R4: 5.6K; R_0603_1608Metric; Ratings ±1%; MPN RMCF0603FT5K60; LCSC C23189
R5: 510K; R_0603_1608Metric; Ratings ±1%; MPN RMCF0603FT510K; LCSC C23192
R6, R7: 75K; R_0603_1608Metric; Ratings ±1%; MPN RMCF0603FT75K0; LCSC C23242
R8: 20K; R_0603_1608Metric; Ratings ±1%; MPN RMCF0603FT20K0; LCSC C4184
R9: 5R1; R_0805_2012Metric; Ratings ±1%; MPN RMCF0805FT5R10; LCSC C17724
R10: 100K; R_0402_1005Metric; Ratings ±1%; MPN RMCF0402FT100K; LCSC C25741
R11: 5R1; R_0805_2012Metric; Ratings ±1%, Pulse-Withstanding; MPN ERJ-P06J5R1V; not fitted
R12, R13: 10K; R_0402_1005Metric; Ratings ±1%; MPN RMCF0402FT10K0; LCSC C25744
R14: 220R; R_0402_1005Metric; Ratings ±1%; MPN RMCF0402FT220R; LCSC C25091
R15: 4K7; R_1206_3216Metric; Ratings ±1% 1/4W; MPN RMCF1206FT4K70; LCSC C17936
TP1: TestPoint; TestPoint_Keystone_5000-5004_Miniature; MPN 5001; Digikey PN 36-5001-ND
TP2: TestPoint; TestPoint_THTPad_D1.0mm_Drill0.5mm
U1: LM5157RTER; QFN_57RTER_TEX_ThermalVias; MPN LM5157RTER; LCSC C5219222
U2: NCP1117-3.3_SOT223; SOT-223-3_TabPin2; MPN NCP1117ST33T3G; LCSC C6186

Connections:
+3.3VA: C12.2, C14.2, FB1.2; also elsewhere on the board
+3V3: C7.1, FB1.1, U2.2 (VO); also elsewhere on the board
+5V: C5.2, C8.1, D3.2 (A), FB2.1, L1.2, Q3.5 (D), R3.1, U1.3 (BIAS); also elsewhere on the board
+5VA: C22.2, C25.2, FB2.2; also elsewhere on the board
+5V_IN: C3.1, C10.2, D1.1 (A1), Q1.1 (S), Q1.2 (S), Q1.3 (S), Q3.1 (S), Q3.2 (S), Q3.3 (S), R13.1, U2.3 (VI); also elsewhere on the board
+12V: C24.1, D4.1 (K), R15.2, TP2.1 (1_1); also elsewhere on the board
+VDC: J1.1, Q1.5 (D)
GND: C3.2, C4.2, C5.1, C7.2, C8.2, C11.2, C12.1, C13.2, C14.1, C15.2, C16.2, C17.2, C18.2, C19.2, C20.2, C21.2, C22.1, C23.2, C24.2, C25.1, C26.2, D1.2 (A2), D4.2 (A), J1.2, J2.2, NT1.2, Q2.2 (S), R10.1, R12.2, R14.2, TP1.1 (1_1), U1.1 (PGND), U1.15 (NC), U1.16 (PGND), U1.17 (EP), U2.1 (GND); also elsewhere on the board
GNDA: C1.2, C2.2, C6.2, NT1.1, R2.2, R4.2, R6.1, R7.1, R8.1, U1.7 (AGND)
LATCH_CONTROL: Q2.1 (G), R12.1; also elsewhere on the board
unnamed: C2.1, R5.2
unnamed: C4.1, R9.2
unnamed: C9.1, R11.2
unnamed: D2.2 (A), L1.1, R11.1, U1.12 (SW), U1.13 (SW), U1.14 (SW)
unnamed: D3.1 (K), R14.1
unnamed: C10.1, J2.1, Q2.3 (D), Q3.4 (G), R13.2
unnamed: Q1.4 (G), R10.2
unnamed: C1.1, R5.1, U1.8 (COMP)
unnamed: R3.2, R4.1, U1.6 (EN/UVLO/SYNC)
unnamed: R1.2, R2.1, U1.9 (FB)
unnamed: R6.2, R7.2, U1.11 (MODE)
unnamed: R8.2, U1.5 (RT)
unnamed: C6.1, U1.10 (SS)
unnamed: R9.1, U1.2 (VCC)
VIR: C9.2, C11.1, C13.1, C15.1, C16.1, C17.1, C18.1, C19.1, C20.1, C21.1, C23.1, C26.1, D2.1 (K), J3.1, R1.1, R15.1; also elsewhere on the board
VIR_RTN: J3.2; also elsewhere on the board

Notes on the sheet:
Traveling at 100 m/s, the maximum pulse width supported over 1 m of travel @ 10A: 23 pulses every 42mm (1 diameter): 30.9us 12 pulses every 84mm (2 diameters): 59.3us
Power Latch
Recommend 16-18 AWG stranded wire Twisted Pair
Power in must be 5.2V
Derated Capacitance (@36V): ~8uF
Analog 5V rail
Reverse Polarity Protection
Recommend 14 AWG stranded wire Twisted Pair
36V Boost Converter @ 0.4A
Analog 3V3 rail
12V Rail
Power LED
Latch bypass
Boost frequency: 1.055 MHz Safe Start Time: 86 ms Turn On Voltage: 4.74V Turn Off Voltage: 4.52V (RPi5 Brown out = 4.64V, fatal shutdown = 4.2V)
3V3 Rail
